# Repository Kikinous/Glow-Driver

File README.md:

# Glow-Driver
Glow Driver for model engine with current sensor

Blog thread: http://www.eevblog.com/forum/projects/improving-glow-plug-drive-design-for-rc-plane-radial-engine/

* eagle file
  - digikey bill of material
  - OSH park PCB manufacture details

* attiny code

* Main computer board

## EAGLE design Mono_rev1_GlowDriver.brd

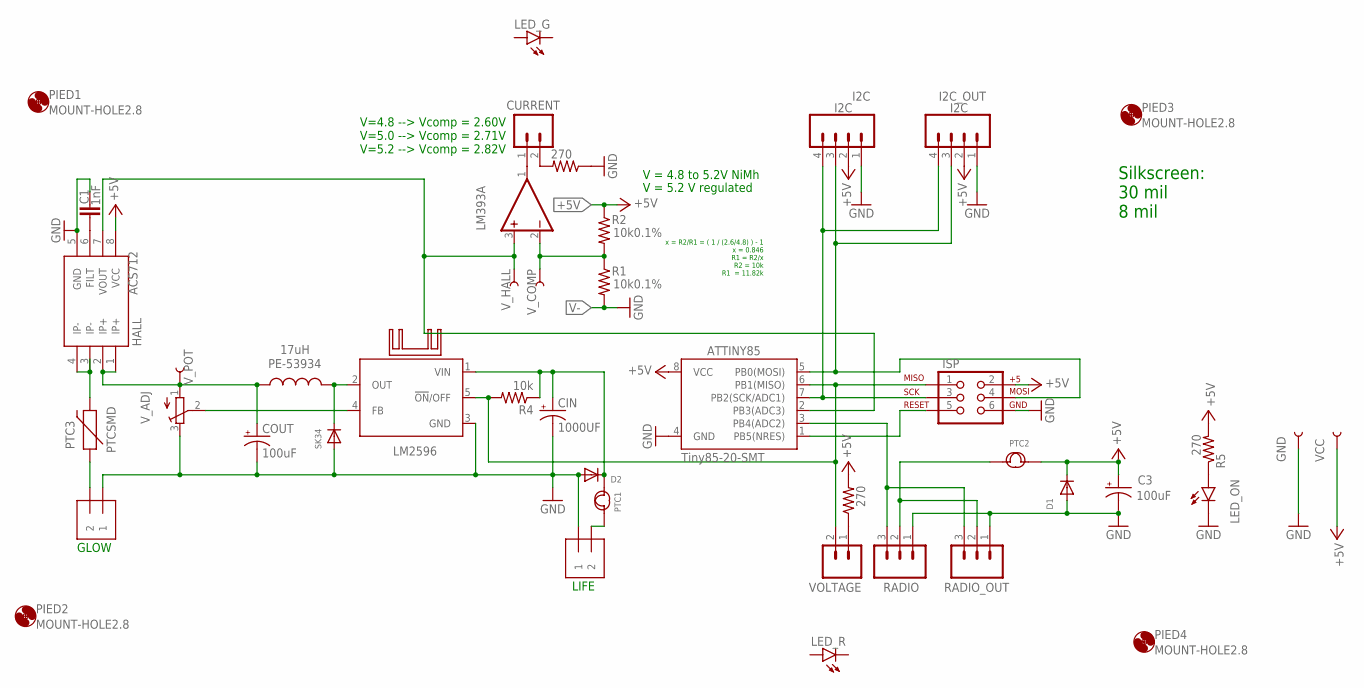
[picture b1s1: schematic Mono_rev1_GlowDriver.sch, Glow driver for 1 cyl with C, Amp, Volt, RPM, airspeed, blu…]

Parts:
ATTINY85: Tiny85-20-SMT; SO08-EIAJ; DIGIKEY ATTINY85-20SU-ND
C1: 1nF; 0805; DIGIKEY 490-11585-1-ND
C3: 100uF; CT3216; DIGIKEY 478-1777-1-ND
CIN: 1000UF; PANASONIC_G; DIGIKEY 493-3930-1-ND
COUT: 100uF; EIA7343; DIGIKEY 478-9193-1-ND
CURRENT: M02PTH; 1X02; DIGIKEY S1011EC-40-ND
D1, D2: DIODESOD-123; SOD-123; DIGIKEY 1N4150W-E3-08CT-ND
GLOW: 1X2-3.5MM; DIGIKEY ED1514-ND
GND: TEST-POINTTP_15TH_THRU; TP_15TH
HALL: ACS712; SO08; DIGIKEY 620-1189-1-ND
I2C, I2C_OUT: I2C; 1X04; DIGIKEY S1011EC-40-ND
ISP: AVR_SPI_PRG_6PTH; 2X3; DIGIKEY 609-2423-ND
KK1: D0A-L; D02A-L; DIGIKEY AE10837-ND
LED_G: LED5MM
LED_ON: LED-GREEN1206; LED-1206; DIGIKEY 404-1046-1-ND
LED_R: LED5MM
LIFE: 1X2-3.5MM; DIGIKEY ED1514-ND
LM393: LM393D; SO08; DIGIKEY 296-1015-5-ND
LM2596: LM2596S; TO263-5; DIGIKEY 296-35399-1-ND
PE-53934: 17uH; LCI-44; DIGIKEY 553-1417-ND
PIED1, PIED2, PIED3, PIED4: MOUNT-HOLE2.8; 2,8
PTC1: 750MA-6V; F1210; DIGIKEY F5766CT-ND
PTC2: 100A-6V; F0805; DIGIKEY 507-1811-1-ND
PTC3: PTCSMD; PTC-1206; DIGIKEY RF2305-000CT-ND
R1, R2: 10k0.1%; 0805; DIGIKEY P10KACT-ND
R3, R5, R6: 270; 0805; DIGIKEY P270ACT-ND
R4: 10k; 0805; DIGIKEY P10KACT-ND
RADIO: M03PTH; 1X03; DIGIKEY S1011EC-40-ND
RADIO_OUT: M03PTH; 1X03; DIGIKEY S1011EC-40-ND
SK34: DIODESMA; SMADIODE; DIGIKEY SK34A-TPCT-ND
VCC: TEST-POINTTP_15TH_THRU; TP_15TH
VOLTAGE: M02PTH; 1X02; DIGIKEY S1011EC-40-ND
V_ADJ: TRIMPOTTC33X; TC33X; DIGIKEY TC33X-103ECT-ND
V_COMP: TEST-POINTTP_15TH_THRU; TP_15TH
V_HALL: TEST-POINTTP_15TH_THRU; TP_15TH
V_POT: TEST-POINTTP_15TH_THRU; TP_15TH

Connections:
+5V: ATTINY85.8 (VCC), C3.+, D1.C, HALL.8 (VCC), I2C.2, I2C_OUT.2, ISP.2, LM393.8 (V+), PTC2.2, R2.1, R3.2, R5.2, VCC.P$1
GND: ATTINY85.4 (GND), C1.1, C3.-, CIN.-, COUT.C (-), D1.A, D2.A, GLOW.1, GND.P$1, HALL.5 (GND), I2C.1, I2C_OUT.1, ISP.6, LED_ON.C, LIFE.1, LM2596.3 (GND), R6.1, RADIO.1, RADIO_OUT.1, SK34.A, V_ADJ.3 (E)
unnamed: R3.1, VOLTAGE.1
unnamed: ATTINY85.3 (PB4(ADC2)), RADIO.3, RADIO_OUT.3
unnamed: ATTINY85.7 (PB2(SCK/ADC1)), I2C.4, I2C_OUT.4, ISP.3
unnamed: ATTINY85.2 (PB3(ADC3)), HALL.7 (VOUT), LM393.3 (+IN), V_HALL.P$1
unnamed: LED_ON.A, R5.1
unnamed: HALL.3 (IP-), HALL.4 (IP-), PTC3.2
unnamed: CURRENT.2, R6.2
unnamed: CURRENT.1, LM393.1 (OUT)
unnamed: LM2596.2 (OUT), PE-53934.P$2 (2), SK34.C
unnamed: GLOW.2, PTC3.1
unnamed: LIFE.2, PTC1.1
unnamed: LM2596.4 (FB), V_ADJ.2 (S)
unnamed: CIN.+, D2.C, LM2596.1 (VIN), PTC1.2, R4.1
unnamed: PTC2.1, RADIO.2, RADIO_OUT.2
unnamed: LM393.2 (-IN), R1.1, R2.2, V_COMP.P$1
unnamed: ATTINY85.5 (PB0(MOSI)), I2C.3, I2C_OUT.3, ISP.4
unnamed: ATTINY85.6 (PB1(MISO)), ISP.1, LM2596.5 (!ON!/OFF), R4.2, VOLTAGE.2
unnamed: C1.2, HALL.6 (FILT)
unnamed: ATTINY85.1 (PB5(NRES)), ISP.5
POT10K: COUT.A (+), HALL.1 (IP+), HALL.2 (IP+), PE-53934.P$1 (1), V_ADJ.1 (A), V_POT.P$1
V-: LM393.4 (V-), R1.2

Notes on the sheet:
GLOW
LIFE
V = 5.2 V regulated
V = 4.8 to 5.2V NiMh
x = R2/R1 = ( 1 / (2.6/4.8) ) - 1 x = 0.846 R1 = R2/x R2 = 10k R1 = 11.82k
V=4.8 --> Vcomp = 2.60V V=5.0 --> Vcomp = 2.71V V=5.2 --> Vcomp = 2.82V
Silkscreen: 30 mil 8 mil

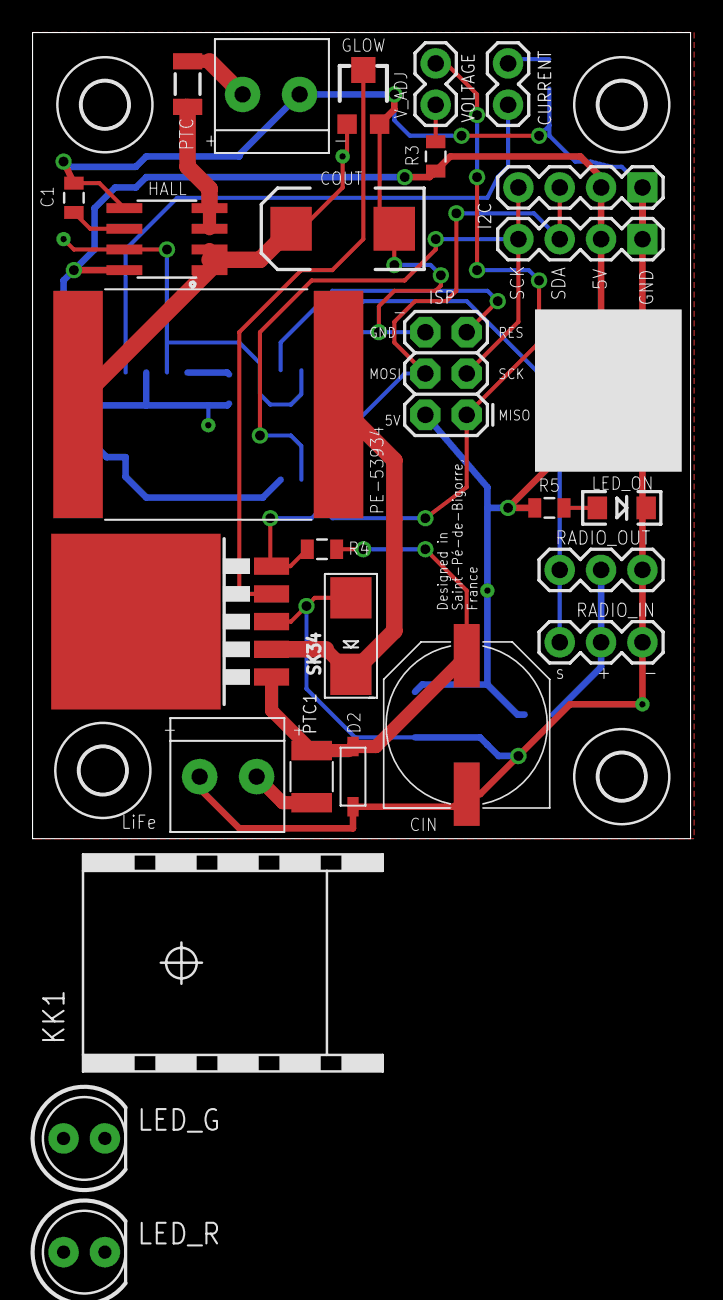
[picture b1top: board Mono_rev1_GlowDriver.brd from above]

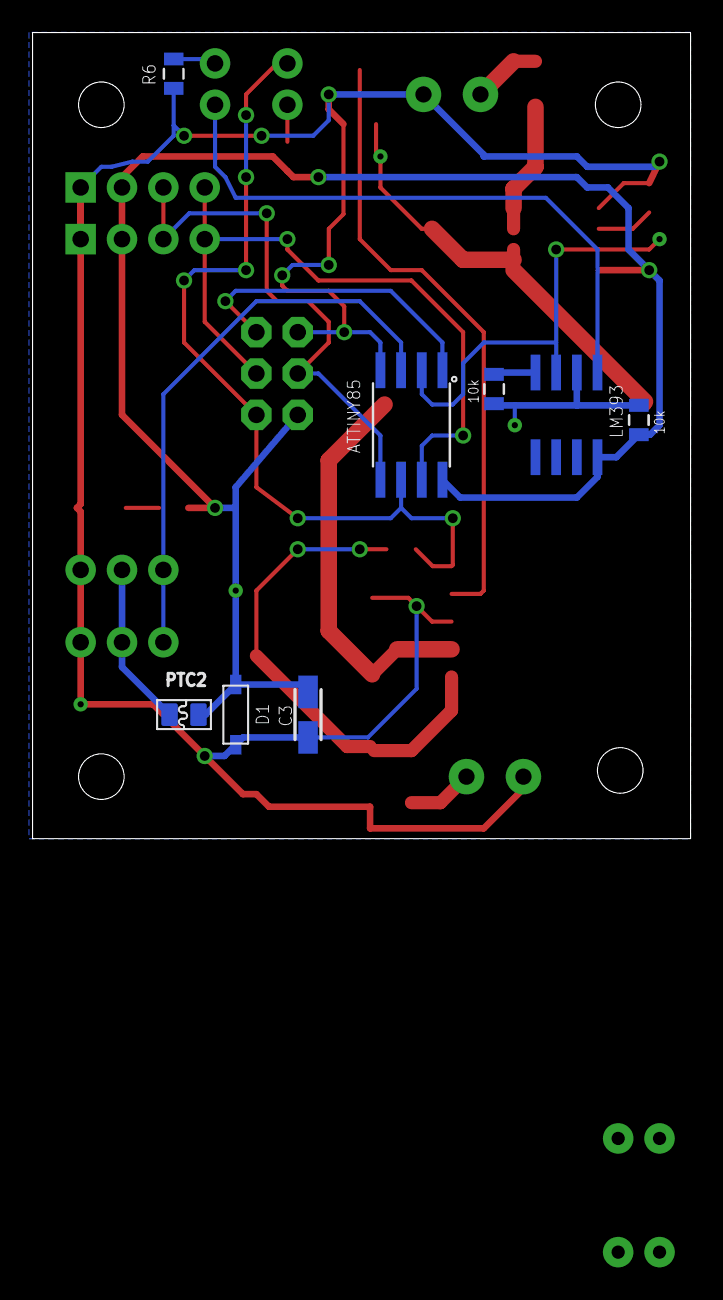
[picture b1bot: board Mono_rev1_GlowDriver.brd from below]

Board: 2 copper layers, 40.4 x 49.5 mm, 44 parts (8 on the bottom side), 23 nets.

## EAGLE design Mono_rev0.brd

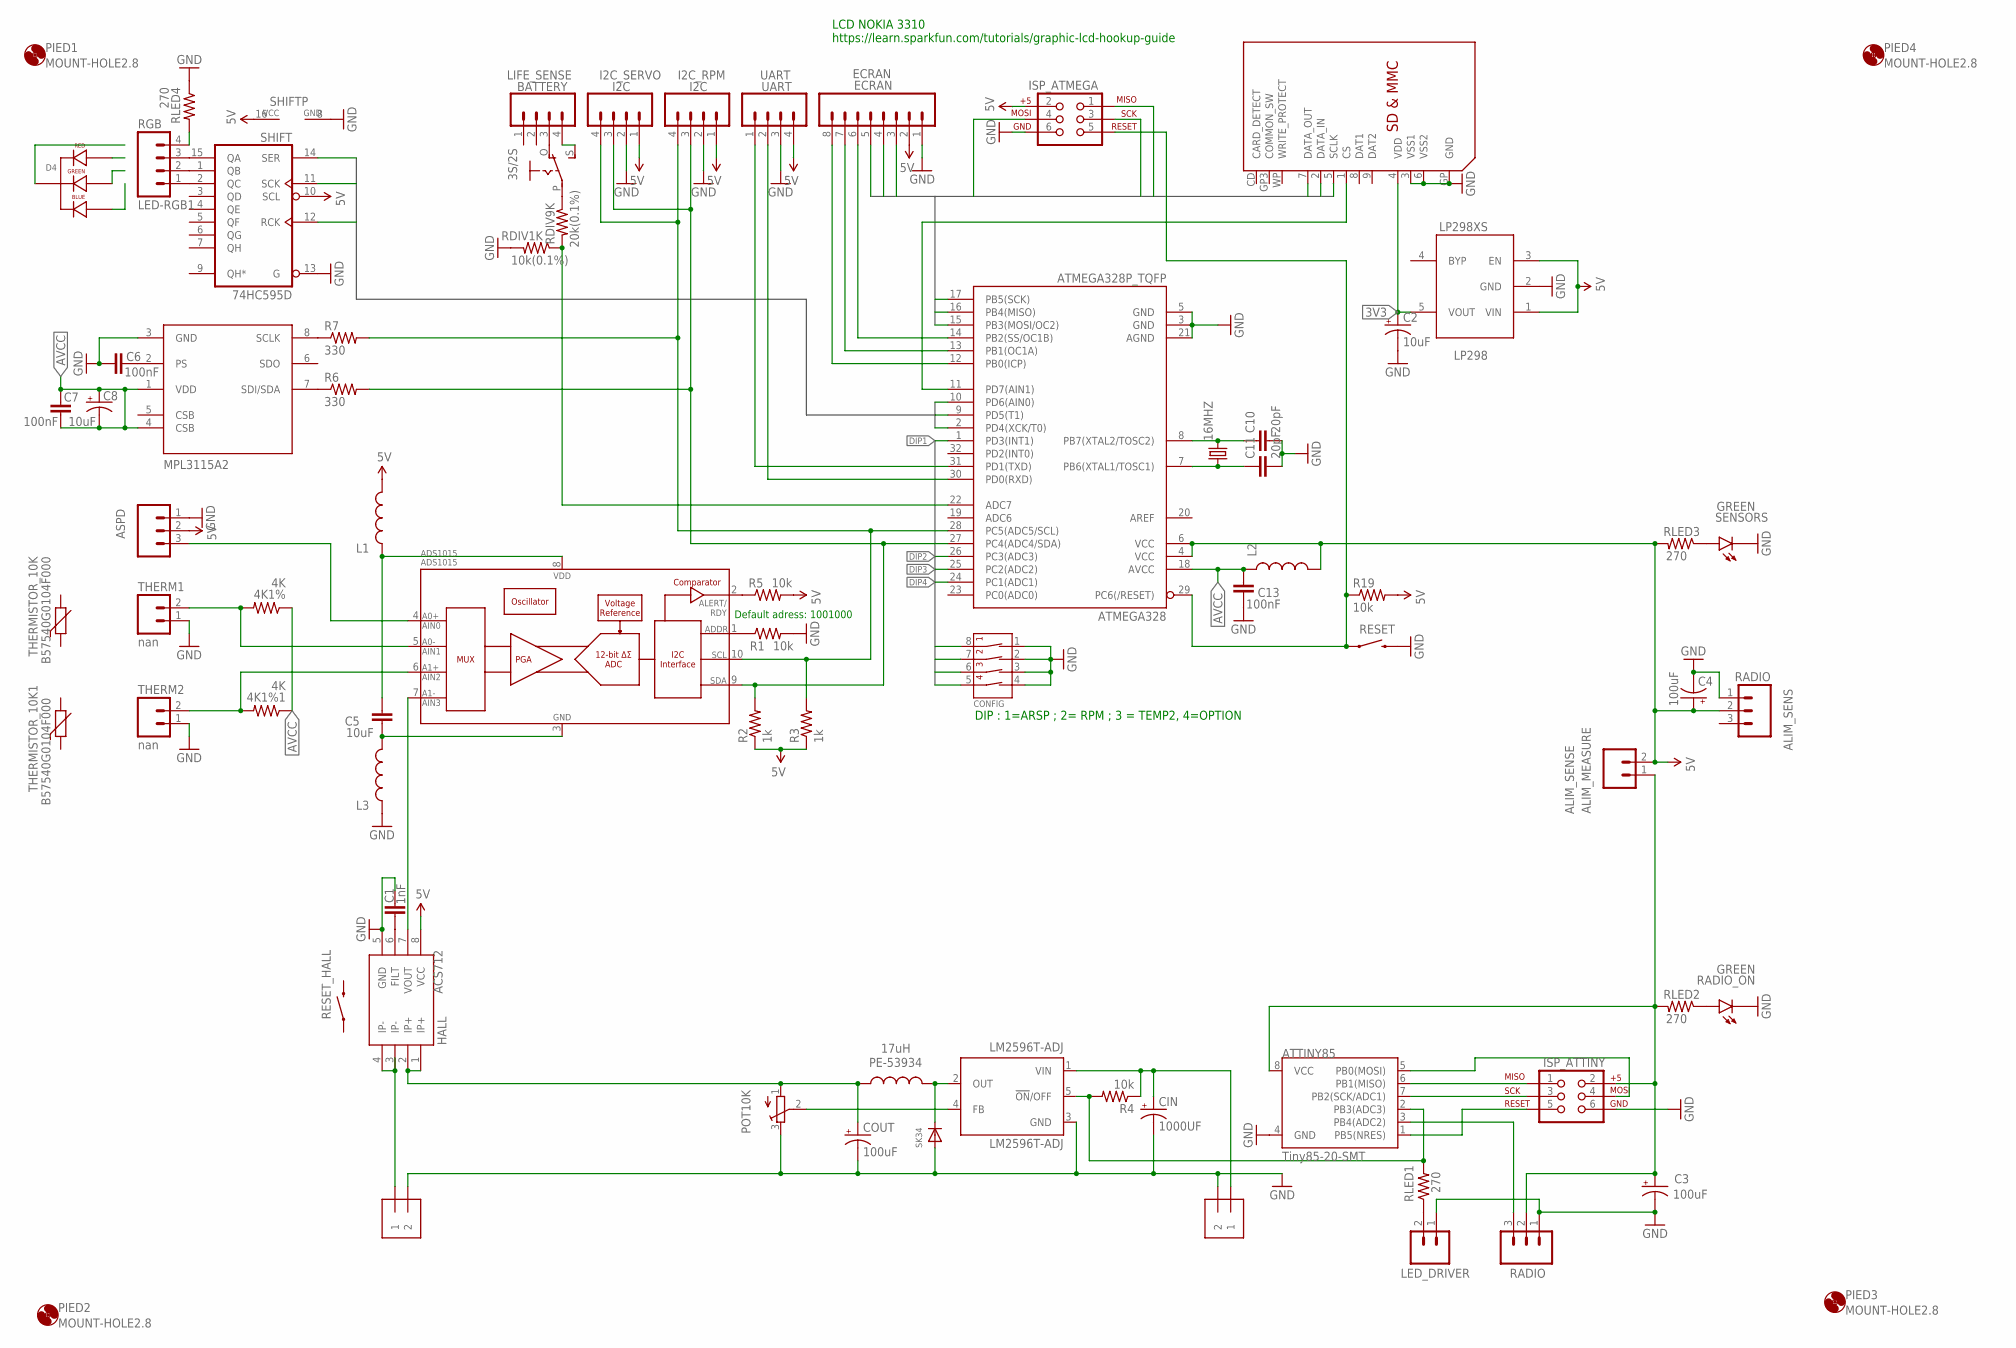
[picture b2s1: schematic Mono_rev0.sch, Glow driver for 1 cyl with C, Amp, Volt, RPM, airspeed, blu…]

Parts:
3S/2S: EG1218S; EG1218; DIGIKEY 679-1854-ND
4K1%, 4K1%1: 4K; 0805; DIGIKEY 274XBK-ND
16MHZ: CRYSTALHC49US; HC49US; DIGIKEY CTX1085-ND
ADS1015: ADS1015; MSOP10; DIGIKEY 296-25227-1-ND
ALIM_SENS: RADIO; 1X03; DIGIKEY S1011EC-40-ND
ALIM_SENSE: ALIM_MEASURE; 1X02; DIGIKEY S1011EC-40-ND
ASPD: M03PTH; 1X03; DIGIKEY S1011EC-40-ND
ATMEGA328: ATMEGA328P_TQFP; TQFP32-08; DIGIKEY ATMEGA328P-AU-ND
ATTINY85: Tiny85-20-SMT; SO08-EIAJ; DIGIKEY ATTINY85-20SU-ND
C1: 1nF; 0805; DIGIKEY 490-11585-1-ND
C2: 10uF; A/3216-18R
C3, C4: 100uF; CT3216; DIGIKEY 478-1777-1-ND
C5: 10uF; 0805; DIGIKEY 490-6472-1-ND
C6, C7, C13: 100nF; 0805; DIGIKEY 490-12558-1-ND
C8: 10uF; EIA3216; DIGIKEY 478-4086-1-ND
C10, C11: 20pF; 0805; DIGIKEY 399-8916-ND
CIN: 1000UF; PANASONIC_G; DIGIKEY 493-3930-1-ND
CONFIG: 4-POS-DIP; 4-POS-DIP-SMD
COUT: 100uF; EIA7343; DIGIKEY 478-9193-1-ND
D4: LED-RGB-CC-THRUDIFFUSE; LED-RGB-THRU; DIGIKEY 754-1492-ND
ECRAN: ECRAN; 1X08; DIGIKEY S1011EC-40-ND
GLOW: 1X2-3.5MM; DIGIKEY ED1514-ND
HALL: ACS712; SO08; DIGIKEY 620-1189-1-ND
I2C_RPM, I2C_SERVO: I2C; 1X04; DIGIKEY S1011EC-40-ND
ISP_ATMEGA: AVR_SPI_PRG_6PTH; 2X3; DIGIKEY 609-2423-ND
ISP_ATTINY: AVR_SPI_PRG_6PTH; 2X3; DIGIKEY 609-2423-ND
L1, L2, L3: INDUCTOR0805; 0805; DIGIKEY MH2029-300YCT-ND
LED_DRIVER: M02PTH; 1X02; DIGIKEY S1011EC-40-ND
LIFE: 1X2-3.5MM; DIGIKEY ED1514-ND
LIFE_SENSE: BATTERY; 1X04; DIGIKEY S1011EC-40-ND
LM2596T-ADJ: LM2596T-ADJ; T05D; DIGIKEY LM2596T-ADJ/NOPB-ND
LP298: LP298XS; SOT23-5L; DIGIKEY 296-18476-1-ND
MPL3115A2: MS5611-01BA03; SON125P300X500X100-8N; DIGIKEY MPL3115A2-ND
PE-53934: 17uH; LCI-44; DIGIKEY 553-1417-ND
PIED1, PIED2, PIED3, PIED4: MOUNT-HOLE2.8; 2,8
POT10K: TRIMPOTTC33X; TC33X; DIGIKEY TC33X-103ECT-ND
R1, R4, R5, R19: 10k; 0805; DIGIKEY P10KACT-ND
R2, R3: 1k; 0805; DIGIKEY P1.0KECT-ND
R6, R7: 330; 0805; DIGIKEY P330ACT-ND
RADIO: M03PTH; 1X03; DIGIKEY S1011EC-40-ND
RADIO_ON: GREEN; LED-1206; DIGIKEY 404-1046-1-ND
RDIV1K: 10k(0.1%); 0805
RDIV9K: 20k(0.1%); 0805
RESET: SWITCH-MOMENTARY-2SMD-1101NE; TACTILE-SWITCH-1101NE
RESET_HALL: SWITCH-MOMENTARY-2SMD-1101NE; TACTILE-SWITCH-1101NE
RGB: LED-RGB1; 1X04; DIGIKEY S1011EC-40-ND
RLED1, RLED2, RLED3, RLED4: 270; 0805; DIGIKEY P270ACT-ND
SENSORS: GREEN; LED-1206; DIGIKEY 404-1046-1-ND
SHIFT: 74HC595D; SO16; DIGIKEY 568-1484-5-ND
SK34: DIODESMA; SMADIODE; DIGIKEY SK34A-TPCT-ND
THERM1, THERM2: nan; 1X02; DIGIKEY S1011EC-40-ND
THERMISTOR_10K, THERMISTOR_10K1: B57540G0104F000; RS-2,5; DIGIKEY 495-2125-ND
U$1: SDMMC06132; 06132
UART: UART; 1X04; DIGIKEY S1011EC-40-ND

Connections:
3V3: C2.+, LP298.5 (VOUT), U$1.4 (VDD)
5V: ALIM_SENS.2, ALIM_SENSE.2, ASPD.2, ATMEGA328.4 (VCC), ATMEGA328.6 (VCC), C4.+, ECRAN.2, HALL.8 (VCC), I2C_RPM.1, I2C_SERVO.1, ISP_ATMEGA.2, L1.2, L2.2, LP298.1 (VIN), LP298.3 (EN), R2.1, R3.1, R5.2, R19.2, RLED3.2, SHIFT.10 (SCL), SHIFT.16 (VCC), UART.4
AVCC: 4K1%.1, 4K1%1.1, ATMEGA328.18 (AVCC), C7.1, C7.2, C8.A (+), C8.C (-), C13.1, L2.1, MPL3115A2.1 (VDD), MPL3115A2.4 (CSB)
DIP1: ATMEGA328.1 (PD3(INT1)), CONFIG.8 (1B)
DIP2: ATMEGA328.26 (PC3(ADC3)), CONFIG.7 (2B)
DIP3: ATMEGA328.25 (PC2(ADC2)), CONFIG.6 (3B)
DIP4: ATMEGA328.24 (PC1(ADC1)), CONFIG.5 (4B)
GND: ALIM_SENS.1, ASPD.1, ATMEGA328.3 (GND), ATMEGA328.5 (GND), ATMEGA328.21 (AGND), ATTINY85.4 (GND), C1.1, C2.-, C3.-, C4.-, C6.1, C10.2, C11.2, C13.2, CIN.-, CONFIG.1 (1A), CONFIG.2 (2A), CONFIG.3 (3A), CONFIG.4 (4A), COUT.C (-), ECRAN.1, GLOW.2, HALL.5 (GND), I2C_RPM.2, I2C_SERVO.2, ISP_ATMEGA.6, ISP_ATTINY.6, L3.1, LED_DRIVER.1, LIFE.2, LM2596T-ADJ.3 (GND), LP298.2 (GND), MPL3115A2.3 (GND), POT10K.3 (E), R1.2, RADIO.1, RADIO_ON.C, RESET.2, RLED4.1, SENSORS.C, SHIFT.8 (GND), SHIFT.13 (G), SK34.A, THERM1.1, THERM2.1, UART.3
LED: LED_DRIVER.2, RLED1.1
MISO: ATMEGA328.16 (PB4(MISO)), ECRAN.4, ISP_ATMEGA.1, U$1.7 (DATA_OUT)
MOSI: ATMEGA328.15 (PB3(MOSI/OC2)), ECRAN.5, ISP_ATMEGA.4, U$1.2 (DATA_IN)
unnamed: ATMEGA328.11 (PD7(AIN1)), U$1.1 (CS)
unnamed: RLED3.1, SENSORS.A
unnamed: RADIO_ON.A, RLED2.1
unnamed: RGB.4, RLED4.2
unnamed: 4K1%1.2, ADS1015.6 (AIN2), THERM2.2
unnamed: ADS1015.7 (AIN3), HALL.7 (VOUT)
unnamed: LM2596T-ADJ.2 (OUT), PE-53934.P$2 (2), SK34.C
unnamed: ATMEGA328.29 (PC6(/RESET)), ISP_ATMEGA.5, R19.1, RESET.1
unnamed: LM2596T-ADJ.4 (FB), POT10K.2 (S)
unnamed: GLOW.1, HALL.3 (IP-), HALL.4 (IP-)
unnamed: ADS1015.1 (ADDR), R1.1
unnamed: ATMEGA328.14 (PB2(SS/OC1B)), ECRAN.6
unnamed: ATMEGA328.13 (PB1(OC1A)), ECRAN.7
unnamed: ATMEGA328.12 (PB0(ICP)), ECRAN.8
unnamed: ADS1015.3 (VSS), C5.2, L3.2
unnamed: 4K1%.2, ADS1015.5 (AIN1), THERM1.2
unnamed: ADS1015.8 (VDD), C5.1, L1.1
unnamed: ADS1015.2 (ALERT/RDY), R5.1
unnamed: 3S/2S.O, LIFE_SENSE.3
unnamed: 3S/2S.S, LIFE_SENSE.4
unnamed: ATMEGA328.22 (ADC7), RDIV1K.1, RDIV9K.2
unnamed: ADS1015.4 (AIN0), ASPD.3
unnamed: MPL3115A2.8 (SCLK), R7.1
unnamed: 3S/2S.P, RDIV9K.1
unnamed: MPL3115A2.7 (SDI/SDA), R6.1
unnamed: C6.2, MPL3115A2.2 (PS)
unnamed: RGB.1, SHIFT.2 (QC)
unnamed: RGB.2, SHIFT.1 (QB)
unnamed: ATTINY85.5 (PB0(MOSI)), ISP_ATTINY.4
unnamed: ATTINY85.6 (PB1(MISO)), ISP_ATTINY.1
unnamed: ATTINY85.7 (PB2(SCK/ADC1)), ISP_ATTINY.3
unnamed: ATTINY85.2 (PB3(ADC3)), LM2596T-ADJ.5 (!ON!/OFF), R4.2, RLED1.2
unnamed: RGB.3, SHIFT.15 (QA)
unnamed: CIN.+, LIFE.1, LM2596T-ADJ.1 (VIN), R4.1
unnamed: ALIM_SENSE.1, ATTINY85.8 (VCC), C3.+, ISP_ATTINY.2, RADIO.2, RLED2.2
unnamed: ADS1015.10 (SCL), ATMEGA328.28 (PC5(ADC5/SCL)), I2C_RPM.4, I2C_SERVO.4, R3.2, R7.2
unnamed: ADS1015.9 (SDA), ATMEGA328.27 (PC4(ADC4/SDA)), I2C_RPM.3, I2C_SERVO.3, R2.2, R6.2
unnamed: C1.2, HALL.6 (FILT)
unnamed: 16MHZ.2, ATMEGA328.8 (PB7(XTAL2/TOSC2)), C10.1
unnamed: 16MHZ.1, ATMEGA328.7 (PB6(XTAL1/TOSC1)), C11.1
unnamed: ATMEGA328.31 (PD1(TXD)), UART.1
unnamed: ATMEGA328.30 (PD0(RXD)), UART.2
unnamed: ATTINY85.1 (PB5(NRES)), ISP_ATTINY.5
unnamed: ATTINY85.3 (PB4(ADC2)), RADIO.3
POT10K: COUT.A (+), HALL.1 (IP+), HALL.2 (IP+), PE-53934.P$1 (1), POT10K.1 (A)
RCK: ATMEGA328.10 (PD6(AIN0)), SHIFT.12 (RCK)
RDIV1K: RDIV1K.2
SCK: ATMEGA328.9 (PD5(T1)), ATMEGA328.17 (PB5(SCK)), ECRAN.3, ISP_ATMEGA.3, SHIFT.11 (SCK), U$1.5 (SCLK)
SER: ATMEGA328.2 (PD4(XCK/T0)), SHIFT.14 (SER)
VSS2: U$1.3 (VSS1), U$1.6 (VSS2), U$1.GP (GND)

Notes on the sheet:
LCD NOKIA 3310 https://learn.sparkfun.com/tutorials/graphic-lcd-hookup-guide
DIP : 1=ARSP ; 2= RPM ; 3 = TEMP2, 4=OPTION
Default adress: 1001000

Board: 2 copper layers, 75 parts (1 on the bottom side), 60 nets, no tracks yet.

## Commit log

2016-06-01 Glow-Driver for RC model engine
    with current sensor / indicator
2016-06-01 cleaning
2016-06-01 remove rev0
    Now rev0 is archived, can be remo
2016-06-01 more cleaning
2016-06-01 add photo
2016-06-01 rotate image
2016-06-01 Revert "rotate image"
    This reverts commit 580dee50fd87ccddde4942fedb95673cd47fdad1.
2016-06-02 main MCU code
2016-06-02 add main board picture
2016-06-02 add readme.md in doc repertory
2016-06-02 add python serial logging sources
2016-06-02 update data
2016-06-02 ATMEGA328P.ino file description
2017-01-26 final

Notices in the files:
parts and their libraries:
SparkFun-FreqCtrl: Licensing: Creative Commons ShareAlike 4.0 International - https://creativecommons.org/licenses/by-sa/4.0
